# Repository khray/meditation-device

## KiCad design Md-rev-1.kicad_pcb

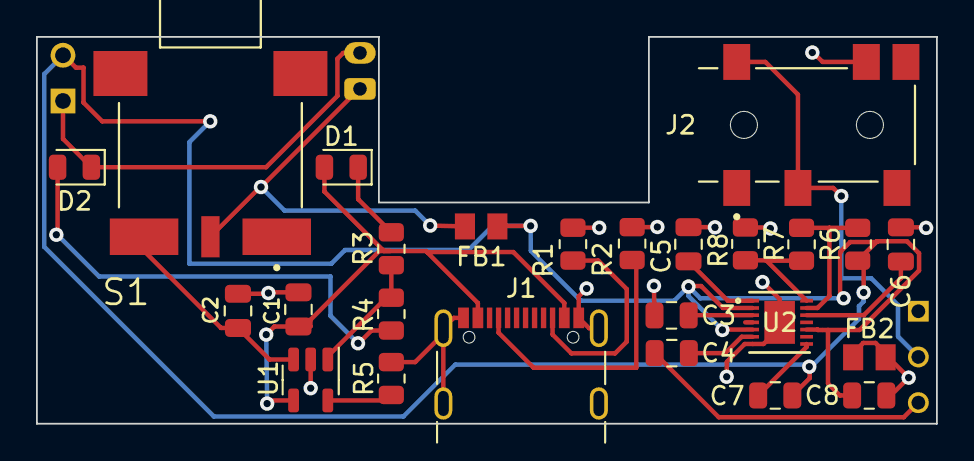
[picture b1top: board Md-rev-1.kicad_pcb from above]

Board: 2 copper layers, 50.0 x 21.5 mm, 25 parts (0 on the bottom side), 20 nets.

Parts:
C1, C2, C4: 10uF; C_0805_2012Metric
C3, C8: 2.2uF; C_0805_2012Metric
C5, C7: 0.1uF; C_0805_2012Metric
C6: 0.47uF; C_0805_2012Metric
D1, D2: LED; LED_0805_2012Metric
FB1, FB2: FERRITE; IND_LI0805H151R-10_LRD
J1: USB_C_Receptacle_USB2.0; USB_C_Receptacle_GCT_USB4105-xx-A_16P_TopMnt_Horizontal
J2: 54-00177; TENSILITY_54-00177
R1, R2: 5.1K; R_0805_2012Metric
R3, R4: 470; R_0805_2012Metric
R5: 2.2k; R_0805_2012Metric
R6: 2.2K; R_0805_2012Metric
R7: 150k; R_0805_2012Metric
R8: 100k; R_0805_2012Metric
S1: 500ASSP1SM6QE; SW_500ASSP1SM6QE
U1: MCP73831-2-OT; SOT-23-5
U2: max9814etd+t; 21-0137I_T1433-2_MXM

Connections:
/5V: C1.2, D1.2 (A), J1.A4 (VBUS), J1.A9 (VBUS), J1.B4 (VBUS), J1.B9 (VBUS), U1.4 (V_{DD})
/VBAT: FB1.1, S1.2
GND: C1.1, C2.2, C3.1, C5.1, C6.1, C8.2, D2.1 (K), FB2.1, FB2.2, J1.A1 (GND), J1.A12 (GND), J1.B1 (GND), J1.B12 (GND), J1.S1 (SHIELD), J2.4, R1.2, R2.2, R5.2, R8.2, U1.2 (V_{SS}), U2.7 (GND), U2.15 (EP)
unnamed: C7.2, R6.1
unnamed: D1.1 (K), R3.2
unnamed: D2.2 (A), R4.2
unnamed: J1.A5 (CC1), R2.1
unnamed: J1.B5 (CC2), R1.1
unnamed: J2.2, J2.3
unnamed: R5.1, U1.5 (PROG)
unnamed: R3.1, R4.1, U1.1 (STAT)
unnamed: C2.1, S1.3, U1.3 (V_{BAT})
unnamed: C6.2, U2.12 (BIAS)
unnamed: C3.2, U2.3 (CG)
unnamed: C5.2, U2.1 (CT)
unnamed: R6.2, R7.1, U2.13 (MICBIAS)
unnamed: C7.1, U2.8 (MICIN)
unnamed: C4.2, U2.6 (MICOUT)
unnamed: R7.2, R8.1, U2.14 (TH)
VDD: C8.1, FB1.2, U2.2 (*SHDN), U2.5 (VDD), U2.10 (GAIN)

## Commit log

2023-12-22 Meditation files
2023-12-22 Updated the PCB design
2024-01-02 Updated the schematic & PCB
2024-01-02 Pushing changes to main
2024-01-02 updated the pill branch
2024-01-03 Updated the footprint files
2024-01-05 reviewing the microphone
2024-01-09 pushing past changes
2024-01-09 updated board
2024-01-12 New meditation device layout
2024-01-17 updated the final design of the pcb
2024-01-19 updated some footprints
2024-01-19 Updated the footprint to reflect the newTRRS headphone jack
2024-01-19 Added the trrs footprint
2024-01-20 swapping out the usb connector
2024-01-23 updating the files for the pcb
2024-01-23 adjusted the placement of the usbc
2024-01-24 updated gerberfiles and symbols
2024-01-28 Updated the pcb for production
2024-01-28 Reorganized the board to meet some of the design rules listed from similar pcb's
2024-01-29 redesigned the pcb to refelct electrical design test
2024-02-01 updated the final PCB
2024-02-01 exported the gerber files
2024-02-01 final save
2024-02-01 Updated the schematif files
2024-02-03 added fabrication file for pick and place
2024-03-26 updating the uncommited files
2024-03-26 updated the schematic and the PCB
